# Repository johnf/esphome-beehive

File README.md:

# ESP32 Beehive Monitor

A battery-powered beehive monitoring system built with ESPHome. Uses FFT-based
audio analysis to detect colony health indicators, along with weight,
temperature, and humidity monitoring.

## Features

- **Audio Analysis**: FFT-based frequency band monitoring to detect queen
  piping, queenless conditions, and pre-swarm behaviour
- **Weight Monitoring**: Track hive weight changes using 4x 50kg load cells via
  NAU7802 ADC
- **Environmental Sensing**: Temperature and humidity via SHT40 sensor
- **Power Monitoring**: Solar current, voltage and power via INA226; battery voltage
  and state of charge via the FeatherS3D's onboard MAX17048 fuel gauge
- **Battery Optimised**: Deep sleep between 5-minute measurement cycles
- **Home Assistant Integration**: Automatic sensor discovery and state reporting

## Hardware Requirements

| Component | Description | Qty |
| ----------- | ------------- | ----- |
| [FeatherS3D](https://unexpectedmaker.com/feathers3d) (ESP32-S3) | Main microcontroller | 1 |
| INMP441 | I2S MEMS microphone (GPIO1, 3, 7) | 1 |
| [Adafruit NAU7802](https://www.adafruit.com/product/4538) | 24-bit ADC breakout | 1 |
| 50kg Load Cells | Half-bridge strain gauges | 4 |
| SHT40 | Temperature/humidity sensor | 1 |
| INA226 | Solar current/voltage/power monitor | 1 |
| CN3065 | Solar LiPo charge controller | 1 |
| [3.7V 2000mAh LiPo](https://core-electronics.com.au/polymer-lithium-ion-battery-2000mah-38459.html) | Battery (DW01+ PCM) | 1 |
| Solar panel | 6V nominal, 1W or larger (CN3065 input is rated for 6V panels) | 1 |
| Stripboard 24 x 41 holes | Main board (under the bottom board) | 1 |
| Stripboard 16 x 15 holes | Hive board (inside the brood box) | 1 |
| JST-XH 8-way socket and cable | Hive cable, one socket per board | 2 sockets, 1 cable |
| JST-XH 12-way socket and cable | Load cell socket (J_CELLS) | 1 |
| JST-XH 2-way socket | Solar in, charger in, charger out | 3 |
| JST-PH 2-way pigtail | CN3065 solar and output sockets | 2 |
| 100 nF ceramic capacitor | C2, C3 | 2 |
| 470 µF 6.3 V electrolytic capacitor | C1 | 1 |

## Power Architecture

The battery is charged by the CN3065 solar charge controller. An INA226 sits
high-side between the solar panel and the CN3065 solar input. The battery connects
directly to the CN3065 battery terminal.

The CN3065 output feeds the FeatherS3D's **VBAT pin**, so the board's own LDO
regulates 3.3V. Feeding the 3.3V pin instead would leave LDO2 unpowered, as its
input is the VBAT/USB node rather than the 3.3V rail.

The FeatherS3D's onboard charger only has power while USB is plugged in, so in the
field the CN3065 is the only charger. On USB, both chargers are 4.2V CC/CV parts and
share the cell harmlessly, with the DW01+ PCM as a backstop.

Battery voltage and state of charge come from the FeatherS3D's onboard MAX17048 fuel
gauge (I2C 0x36), which sees the cell via the VBAT pin. It sits on the always-on
LDO1 rail, so its ModelGauge state survives deep sleep.

The FeatherS3D's **LDO2** (GPIO39) provides a switchable 3.3V rail that is automatically
disabled during deep sleep, used to power-gate sensors that aren't needed during sleep.
All sensors, including the I2C pull-ups on their breakouts, are on this rail.

The INA226 address pins A0 and A1 are left unconnected. The CJMCU-226 module
has 10 kΩ pull-downs on both, which gives address 0x40. Confirm this on your
unit before building: unpowered, A0 to GND and A1 to GND should each read about
10 kΩ. If either reads open, strap that pad to GND.

CJMCU-226 modules come with two header pinouts: after ALE some read SDA then
SCL, others SCL then SDA. The Fritzing part (`fritzing/ina226/`) and the
stripboard layout follow the first, with SDA on pin 5. Check the silkscreen
before soldering the header; if yours is the other variant, do not plug the
module straight into its socket, but cross SDA and SCL with two short flying
leads.

### Solar Performance

The CN3065 regulates its own input voltage. In direct sun it held the panel at
4.77V for over an hour while the current drifted, well below the 6V maximum
power point of a nominal 6V panel. Panel power is therefore capped near 0.8W no
matter how much sun a 1W panel sees.

That cap matters less than it looks. The CN3065 is a linear charger, so it
passes current through roughly one-for-one and burns the voltage difference as
heat. Charge current, not panel watts, is what fills the cell.

Measured on a 110 x 60 mm 1W 6V polycrystalline panel in direct spring sun
(Sydney, sun about 52° above the horizon, panel not aimed):

| Quantity | Value |
|----------|-------|
| Panel voltage | 4.77V (clamped by the CN3065) |
| Panel current | 113-121 mA |
| Panel power | 0.54-0.58W |
| Fraction of nameplate | 55-58% |

At ~113 mA against an average draw of ~2.3 mA, roughly half an hour of direct
sun per day covers the device's entire daily consumption, and four good hours
put in over eight times what it uses. A 1W panel is ample for this load.

Siting buys far more than panel size. The same panel shaded and badly angled
produced 5-50 mW, one to two orders of magnitude below its direct-sun output,
and the battery fell 2.7% per day through it. If the battery is losing ground,
move the panel before buying a bigger one.

If you do want more margin, wire two panels in **parallel** to roughly double
the current at the clamped voltage. Series gains nothing, because the charger
regulates its input down regardless of what the panels could deliver.

### Battery Specifications

| Parameter | Value |
|-----------|-------|
| Nominal voltage | 3.7V |
| Charge voltage | 4.2V (CN3065) |
| Overcharge protection | 4.30V ±0.05V (DW01+ PCM) |
| Over-discharge protection | 2.4V ±0.1V (DW01+ PCM) |
| Capacity | 2000mAh |
| Wiring/connector rating | 1A max |

### I2C Address Map

| Address | Device |
|---------|--------|
| 0x2A | NAU7802 (load cell ADC) |
| 0x36 | MAX17048 fuel gauge (onboard FeatherS3D) |
| 0x40 | INA226 (solar) |
| 0x44 | SHT40 (temperature/humidity) |

## Wiring

The circuit is split across two stripboards joined by a pluggable cable. The
Fritzing sketch `fritzing/BeeHive.fzz` is the design of record and its
breadboard view holds the stripboard layout. Both boards use vertical strips
(strips run top to bottom in the breadboard view) and hole coordinates below
are `(column, row)` counted from 0 at the top-left.

### Boards and Connectors

**Main board** (24 x 41, under the bottom board with the battery, CN3065 and
solar panel plug): FeatherS3D, INA226, NAU7802, C1, C2 and five sockets. The
Feather sits across the top with its 16-pin row on row 3 and 12-pin row on
row 11; every strip under those rows is cut above the top row and below the
bottom row (cuts `x.3v` and `x.10v` for columns 3-18 and 3-14) so the two rows
do not short, except column 15, which carries the Feather GND pin the full
height of the board as the ground rail. Column 2 is the 3.3 V rail, fed from
LDO2 (column 3, row 3) by the jumper on row 2.

Columns 2-9 run straight from the Feather's bottom row to J_HIVE on the bottom
edge (row 40), so 3V3, SDA, SCL, WS, SCK and SD reach the hive socket without a
jumper; columns 5 and 6 (IO33 and IO38, cut at `5.11v 6.11v`) become its two
ground pins via row 14. Everything else sits to the right of that corridor:
C1 and the VBAT tap at the top right, J_PWR on the right edge at row 15, the
INA226 with its header on row 18 (VCC, GND, SCL, SDA, ALE, VBS, IN-, IN+ on
columns 14-21, GND landing on the rail, C2 directly above it on row 17),
J_SOLAR and J_CHG on the right edge at rows 28 and 31, the NAU7802 with its
header on row 29 (DRDY, SDA, SCL, GND, AVDD, VCC on columns 12-17, GND on the
rail, screw terminal facing the bottom edge) and J_CELLS on the bottom edge
beside J_HIVE. Column 23 is a second ground rail for C1 and the three
right-edge sockets; column 22 carries VBAT, panel + and charger + in three
segments. Row 39 stays empty under the two bottom sockets.

| Row | Jumper | Net |
| --- | ------ | --- |
| 2 | (3,2) → (2,2) | LDO2 to the 3.3 V rail |
| 12 | (14,12) → (22,12) | VBAT to C1 and J_PWR |
| 13 | (2,13) → (14,13) | 3.3 V to INA226 VCC and C2 |
| 13 | (15,13) → (23,13) | Ground to the right rail |
| 14 | (15,14) → (6,14) → (5,14) | Ground to J_HIVE pins 4 and 5 |
| 15 | (4,15) → (16,15) | SCL to the INA226 |
| 16 | (3,16) → (13,16) → (17,16) | SDA to the NAU7802 and INA226 |
| 26 | (14,26) → (17,26) | 3.3 V to NAU7802 VCC |
| 26 | (19,26) → (20,26) | INA226 VBS to IN- |
| 26 | (21,26) → (22,26) | INA226 IN+ to J_SOLAR + |
| 27 | (16,27) → (14,27) | SCL to the NAU7802 |
| 33 | (20,33) → (22,33) | INA226 IN- to J_CHG + |
| 38 | (12,38) → (13,38), (15,38) → (16,38), (18,38) → (19,38), (21,38) → (22,38) | Load cell ring, see [Load Cells](#load-cells) |
| 38 | (11,38), (14,38), (17,38), (20,38) | Flying leads into the NAU7802 screw terminal |

**Hive board** (16 x 15, inside the brood box): SHT40, INMP441, C3 and the
cable socket. It is wired up the inside of the hive and unplugs at the main
board.

| Socket | Board, holes | Pin 1 | Pin 2 | Pin 3 | Pin 4 | Pin 5 | Pin 6 | Pin 7 | Pin 8 |
| --- | --- | --- | --- | --- | --- | --- | --- | --- | --- |
| J_HIVE | Main (2-9, 40) | 3V3 | SDA | SCL | GND | GND | WS | SCK | SD |
| J_SUB | Hive (2-9, 1) | 3V3 | SDA | SCL | GND | GND | WS | SCK | SD |
| J_SOLAR | Main (22-23, 28) | Panel + | Panel - | | | | | | |
| J_CHG | Main (22-23, 31) | CN3065 SOLAR + | CN3065 SOLAR - | | | | | | |
| J_PWR | Main (22-23, 15) | CN3065 OUT + | CN3065 OUT - | | | | | | |
| J_CELLS | Main (11-22, 40) | 12 pins, see [Load Cells](#load-cells) | | | | | | | |

The hive cable is wired pin for pin. Ground sits between SCL and the I2S
clocks so the cable can run a metre or two. With Cat5e or Cat6, pair the wires
by signal, not in T568A/B order, which puts SCL with WS and SCK with SD:

| Pair | Pin | Signal | Colour |
| --- | --- | --- | --- |
| Blue | 7 | SCK | Blue |
| | 4 | GND | White/blue |
| Green | 3 | SCL | Green |
| | 5 | GND | White/green |
| Orange | 2 | SDA | Orange |
| | 1 | 3V3 | White/orange |
| Brown | 6 | WS | Brown |
| | 8 | SD | White/brown |

Each clock shares its pair with a ground. WS and SD can share a pair because
both change on the falling edge of SCK and SD is read on the rising edge. Keep
the untwisted length at each connector under about 15 mm.

JST-XH is 2.5 mm pitch, which
fits the 2.54 mm stripboard grid with a little lean on the 8-way socket and
about half a millimetre over the 12-way. Every socket sits on a board edge, so
side-entry (S*B-XH-A) or top-entry (B*B-XH-A) housings both work.

The CN3065 module is not on the stripboard. Its three JST-PH sockets take the
panel current from J_CHG (after the INA226 shunt), the battery directly, and
send the output to J_PWR via short pigtails. The INA226 address pads A0 and A1
are left open; the module pulls them down (see Power Architecture).

Strip cuts on the main board beyond the Feather rows: `5.11v 6.11v` turn the
IO33 and IO38 strips into the J_HIVE grounds, `14.12v` separates VBAT from the
3.3 V segment that feeds the INA226, `13.15v 16.14v 17.15v` keep the SDA and
SCL taps off the Feather pins and pads above them, `17.25v 14.26v 16.27v
12.28v` split the INA226 columns from the NAU7802 header (VCC, SCL, AVDD and
DRDY), `22.15v 22.29v` divide column 22 into VBAT, panel + and charger +, and
`11.37v` to `22.37v` isolate the J_CELLS pins (rows 38-40) from everything
above them. On the hive board the cuts are `6.4v` (SHT40 VIN off the ground
strip) and `10.6v 11.6v` (the microphone's top and bottom pin rows). The
sketch has the jumper wires and exact placements; check the build against it
with `python3 .claude/skills/circuit/fzz_nets.py fritzing/BeeHive.fzz`.

### I2C Bus (SHT40, NAU7802, INA226, MAX17048)

The I2C bus must be defined in your device configuration and its `id` passed to the
package via the `i2c_bus_id` substitution (defaults to `i2c_bus`).

| Signal | Default GPIO |
| -------- | ------------ |
| SDA | GPIO8 |
| SCL | GPIO9 |

### INMP441 Microphone

Pin assignments are configurable via substitutions (`i2s_lrclk_pin`, `i2s_bclk_pin`, `i2s_din_pin`).

| INMP441 Pin | Default ESP32 GPIO |
| ------------- | ------------ |
| WS (LRCLK) | GPIO1 |
| SCK (BCLK) | GPIO3 |
| SD (DOUT) | GPIO7 |
| VDD | 3.3V |
| GND | GND |
| L/R | GND (left channel) |

### Load Cells

Each 50kg half-bridge cell has three wires: red (centre tap), white and black.
All twelve go to J_CELLS, the 12-way JST-XH socket on the bottom edge of the
main board. The bridge is made on the board, so nothing is spliced at the
platform. Place one cell at each corner and number them 1 to 4 clockwise.

| J_CELLS pin | Wire | J_CELLS pin | Wire |
| ----------- | ---- | ----------- | ---- |
| 1 | Cell 1 red | 7 | Cell 3 red |
| 2 | Cell 1 white | 8 | Cell 3 white |
| 3 | Cell 2 white | 9 | Cell 4 white |
| 4 | Cell 2 red | 10 | Cell 4 red |
| 5 | Cell 2 black | 11 | Cell 4 black |
| 6 | Cell 3 black | 12 | Cell 1 black |

The jumpers on row 38 bridge pins 2-3, 5-6, 8-9 and 11-12, joining like
colours round the platform (white 1-2, black 2-3, white 3-4, black 4-1) into a
full Wheatstone bridge. Like must join like: in each cell the white and black
halves change in opposite directions under load, so a white-to-black ring
cancels in every bridge arm and the output barely moves. The four red wires
land on row 38 under the NAU7802 screw terminal and run into it with short
leads:

| Cell (red wire) | Row 38 hole | NAU7802 |
| --------------- | ----------- | ------- |
| Cell 1 | (11,38) | E+ |
| Cell 2 | (14,38) | A- |
| Cell 3 | (17,38) | E- |
| Cell 4 | (20,38) | A+ |

E+ and E- are the bridge excitation (the breakout's AVDD and GND); A- and A+
are the channel A input. The B- and B+ terminals are the unused channel B.

If the weight reads negative when load is added, swap A+ and A-.

### Capacitors

| Ref | Value | Placement |
| --- | ----- | --------- |
| C1 | 470 µF electrolytic, 6.3 V | VBAT and GND strips at the top right, main board (22-23, 11) |
| C2 | 100 nF ceramic | INA226 VCC and GND strips directly above its header, main board (14-15, 17) |
| C3 | 100 nF ceramic | INMP441 VDD and GND strips, hive board (11-12, 10) |

C1 stops WiFi transmit bursts browning out the LDO when the cell is cold or low.
C2 and C3 must sit right at the module pins; long wires in a beehive pick up
noise, and the INMP441 feeds the FFT analysis. The NAU7802 and SHT40 breakouts
have onboard decoupling already.

## Enclosure

`case/beehive-case.scad` is a parametric OpenSCAD model of two enclosures, with
exported STLs in `case/stl/`. Every dimension is a named variable at the top of
the file.

The `layout` view shows where the boards, battery and charger sit:

After changing a dimension, re-export the STLs and images:

```bash
cd case
for p in box lid clamp foot hive_base hive_lid; do
  openscad -D "part=\"$p\"" -o stl/$p.stl beehive-case.scad
done
openscad -D 'part="layout"' --camera=0,0,0,50,0,25,600 --viewall --autocenter \
  --imgsize=1600,1100 --colorscheme=Tomorrow -o images/layout.png beehive-case.scad
openscad -D 'part="layout"' --camera=0,0,0,0,0,0,600 --projection=ortho --viewall \
  --autocenter --imgsize=1600,1100 --colorscheme=Tomorrow -o images/layout-top.png \
  beehive-case.scad
openscad -D 'part="assembly"' --camera=0,0,0,50,0,25,600 --viewall --autocenter \
  --imgsize=1600,1100 --colorscheme=Tomorrow -o images/assembly.png beehive-case.scad
openscad -D 'part="seal_section"' --camera=0.99,37.98,0,0,0,0,40 --projection=ortho \
  --imgsize=1600,1100 --colorscheme=Tomorrow -o images/seal-section.png \
  beehive-case.scad
for p in hive_base hive_lid; do
  openscad -D "part=\"$([ $p = hive_lid ] && echo hive_lid_fitted || echo $p)\"" \
    --camera=0,0,0,50,0,25,150 --viewall --autocenter --imgsize=1600,1100 \
    --colorscheme=Tomorrow -o images/${p/_/-}.png beehive-case.scad
done
```

Then slice every STL with PrusaSlicer to catch parts that don't fit the bed or
need supports. `a1mini.ini` approximates the A1 mini with the settings below and
gives print times and filament use:

```bash
for p in box lid clamp foot hive_base hive_lid; do
  prusa-slicer --export-gcode --load a1mini.ini --center 90,90 \
    -o /tmp/$p.gcode stl/$p.stl 2>&1 | grep -A3 -i warning
done
```

`hive_lid` reports "Floating bridge anchors": that is the one-layer bridge over
each counterbore that you drill out, and it prints fine.

Open `beehive-case.scad` in OpenSCAD with `part = "layout"` to rotate the layout
view yourself. Colours only show in preview (F5), not in a full render (F6).

**Main box** sits under the hive and holds the main board, battery and CN3065.
The board rides on two M3 posts down its left edge and two printed clamps on its
right edge, with the battery and charger underneath. There is 30 mm clearance on
the terminal edges. Cables enter through two PG9 glands and a PG7 on one long wall; an
M12 ePTFE vent on the end wall lets it breathe without leaving a gap for ants. A
2.4 mm O-ring sits in a groove in the rim. The lid closes flush on the rim,
which squeezes the ring 25%, and screws into heat-set inserts in eight lugs. A
skirt under the lid locates it inside the walls, and a lip around its edge
stiffens it and keeps rain off the rim.

The seal is a 155 mm OD x 2.4 mm nitrile O-ring (about 150 mm ID). It stretches
about 2% to fit the groove, whose centre line is 488 mm (`groove_len`). A larger
2.4 mm ring or cord also works: cut it to 488 mm and butt-join the ends with
cyanoacrylate. For a different cross-section, change `oring_d`, `groove_depth`
(0.75 x the cross-section, rounded to a multiple of the layer height) and
`groove_w` (1.3 x).

**Hive housing** sits loose on the mesh floor inside the brood box. The base is
solid so the SHT40 reads hive air, not air through the mesh. The board rests on
ledges and ribs on the lid's side walls hold it down. The top and sides are a
grid of 2 mm holes, too small for bees. The Cat6 leaves through a notch at one
end, tied to an anchor.

Print in PLA, starting from the A1 mini 0.20 mm Standard profile with 4 wall
loops, 35% infill and no brim (`box` and `lid` are 175 mm long on a 180 mm
bed). Iron the top surface of `lid`, which is its sealing face. Print `lid` and
`hive_lid` as exported (outside face down). Each screw hole in `hive_lid` has a one-layer
bridge at the bottom of its counterbore; push a 3 mm drill through it after
printing. Press the heat-set inserts into the lid lugs, board posts, clamp
towers and hive housing posts with a soldering iron before assembly, flush or
just below the surface; the lid must sit flat on the lugs.

| Part | Qty |
| ---- | --- |
| `box`, `lid`, `hive_base`, `hive_lid` | 1 each |
| `clamp` | 2 |
| `foot` (glue into the floor) | 4 |
| PG9 cable gland, 4-8 mm (load cells, Cat6) | 2 |
| PG7 cable gland, 3-6.5 mm (solar) | 1 |
| M12 ePTFE breather vent | 1 |
| M3 x 10 socket head cap screw, stainless | 14 |
| M3 x 5.7 mm heat-set insert, 4.0 mm hole (e.g. ruthex) | 14 |
| O-ring, 155 mm OD x 2.4 mm, nitrile | 1 |
| Adhesive-lined heatshrink (load cell bundle, solar pair) | 2 |
| Silica gel sachet | 1 |
| Removable double-sided mounting strip (battery to floor, e.g. 3M Command) | 1 |

Drill the main board's two M3 holes in the outer left column, 15 mm and 73 mm
from the bottom edge. If you drill elsewhere, update `left_holes_y`.

## Installation

### Prerequisites

- Home Assistant with the ESPHome add-on installed

### Setup

1. **Create a new device in ESPHome**

   - Open the ESPHome dashboard in Home Assistant
   - Click **+ New Device**
   - Choose **Continue** then **Skip this step** (we'll use our own config)
   - Enter a name (e.g., `beehive-monitor`) and click **Next**
   - Select **ESP32** as the device type
   - Click **Skip** to skip the installation for now

2. **Edit the configuration**

   Click **Edit** on the new device and use the following configuration:

   ```yaml
   # Include the beehive monitoring package. `refresh: always` re-fetches the
   # default branch on every run instead of using ESPHome's cached copy.
   packages:
     beehive:
       url: https://github.com/johnf/esphome-beehive
       files: [beehive-monitor.yaml]
       refresh: always

   # Device configuration (required)
   esphome:
     name: beehive-monitor
     friendly_name: Beehive Monitor

   esp32:
     framework:
       type: esp-idf
     variant: esp32s3
     flash_size: 16MB  # FeatherS3D has 16MB flash

   psram:
     mode: quad
     speed: 80MHz

   # I2C bus (required - must define with id matching i2c_bus_id substitution)
   i2c:
     id: i2c_bus
     sda: GPIO8
     scl: GPIO9
     scan: true
     frequency: 400kHz

   # WiFi configuration (required)
   wifi:
     ssid: !secret wifi_ssid
     password: !secret wifi_password
     fast_connect: true

   # Home Assistant API (required)
   api:
     reboot_timeout: 0s

   # Optional: enable logging during development
   logger:
     hardware_uart: USB_CDC
     level: DEBUG

   # Optional: override default pin assignments, I2C addresses, calibration
   # or audio thresholds (see beehive-monitor.yaml for the full list)
   # substitutions:
   #   i2c_bus_id: "i2c_bus"
   #   i2s_lrclk_pin: "GPIO1"
   #   i2s_bclk_pin: "GPIO3"
   #   i2s_din_pin: "GPIO7"
   #   ina226_solar_address: "0x40"
   #   audio_active_threshold: "-95dB"
   ```

   A complete working example is in [example.yaml](example.yaml).

3. **Configure secrets**

   ESPHome uses Home Assistant's secrets. Add to your `secrets.yaml`:

   ```yaml
   wifi_ssid: 'YourWiFiNetwork'
   wifi_password: 'YourWiFiPassword'
   ```

   Or use the ESPHome Secrets editor (three-dot menu → **Secrets**).

4. **Install to the device**

   - Click **Install** on the device
   - For first-time installation, choose **Plug into this computer** or
     **Manual download** to get the firmware binary
   - Flash via USB using the web installer at <https://web.esphome.io/>
   - Subsequent updates can use **Wirelessly** once connected; see
     [OTA Updates](#ota-updates) for how to keep the device awake

### OTA Updates

The device is only awake for a few seconds every five minutes, which is not long
enough to install firmware wirelessly. The package therefore reads a Home
Assistant boolean helper on every wake and stays awake while it is on.

1. In Home Assistant, go to **Settings → Devices & services → Helpers**, create a
   **Toggle** helper and name it `Beehive OTA mode`, so its entity ID is
   `input_boolean.beehive_ota_mode`. Use the `ota_mode_entity` substitution if
   you pick a different name or run several hives.

   Then go to **Settings → Devices & services → ESPHome**, open the device's
   integration entry, click **Configure** and enable **Allow the device to
   perform Home Assistant actions**. The device needs this to clear the helper
   if it's left on (see below).
2. Turn the helper on. Within five minutes the device wakes, sees it, and logs
   `OTA mode - staying awake`. It keeps taking readings every
   `ota_mode_interval` (default five minutes); the **Measure Now** button
   starts a cycle straight away.
3. Click **Install → Wirelessly** in the ESPHome dashboard. Once an upload
   starts the device will not sleep until it reboots into the new firmware.
4. After the reboot the device stays awake while the helper is on, so you can
   watch the logs. Turn the helper off and the device goes back to sleep
   straight away.

If the helper is left on, the device clears it after `ota_mode_max_awake`
(default 30 minutes) and goes back to sleep. Without the actions permission
from step 1 the device still sleeps after the timeout, but stays awake again on
the next wake until you turn the helper off.

To check which commit a device is running, look at **Firmware** on the device
page in Home Assistant, or for `Project johnf.esphome-beehive version <commit>`
in the boot log. A `-dirty` suffix means it was built from a checkout with
uncommitted changes.

The package defines the `ota` component. To add a password or other options,
extend it in your device configuration rather than declaring a second one:

```yaml
ota:
  - id: !extend ota_esphome
    password: !secret ota_password
```

### Power Optimisation (recommended for battery operation)

For battery-powered deployments, add these settings to reduce power consumption:

```yaml
wifi:
  ssid: !secret wifi_ssid
  password: !secret wifi_password
  fast_connect: true
  power_save_mode: light
  # Static IP eliminates DHCP negotiation, saving 1-3 seconds per wake
  manual_ip:
    static_ip: 192.168.1.100  # Choose an IP outside your DHCP range
    gateway: 192.168.1.1      # Your router's IP
    subnet: 255.255.255.0

api:
  reboot_timeout: 0s  # Prevent reboots when Home Assistant is unavailable

# Disable UART logging in production
logger:
  level: WARN
  baud_rate: 0
```

## Calibration

### Load Cell Calibration

The package ships with placeholder calibration values that will not match your
load cells. Calibrate before trusting any weight reading.

1. Turn on [OTA mode](#ota-updates) so the device stays awake, and view the
   device logs in the ESPHome dashboard (click **Logs**). Each measurement
   cycle logs seven raw NAU7802 values; use the middle of the range. Cycles
   repeat every `ota_mode_interval` (default 5 minutes); set it to `10s` while
   calibrating for quicker readings, or press the **Measure Now** button on
   the device page in Home Assistant to start a cycle immediately
2. With no weight on the platform, note the raw value
3. Place a known weight on the platform and note the raw value. Use at least
   20 kg so the calibration spans a realistic hive weight; a second known
   weight (e.g. 40 kg) improves accuracy further
4. Let the platform settle for a minute after each change before reading
5. Click **Edit** on the device and set the calibration substitutions:

   ```yaml
   substitutions:
     weight_cal_raw_1: "<raw_empty>"
     weight_cal_kg_1: "0"
     weight_cal_raw_2: "<raw_20kg>"
     weight_cal_kg_2: "20"
     weight_cal_raw_3: "<raw_40kg>"
     weight_cal_kg_3: "40"
     weight_cal_raw_4: "<raw_40kg>"
     weight_cal_kg_4: "40"
   ```

   A least-squares line is fitted through the four points, so repeating a
   point is fine if you only have two known weights.

6. Click **Install** → **Wirelessly** to update the device

### Audio Baseline

Frequency band levels are reported as mean power spectral density in dB
relative to full scale (dB re FS²/Hz). This is independent of `fft_size` and
`frames`, so thresholds survive changes to those settings. Sound Level is
plain dBFS, measured above 60 Hz so the microphone's DC offset is excluded. The INMP441 reaches full scale at roughly 120 dB SPL, so add 120
to convert either figure to an approximate sound pressure level.

Each reading averages four consecutive FFT frames (about one second of audio).
Increase `audio_frames` for steadier band levels at the cost of awake time.

The Modulation Index and Modulation Frequency sensors come from a separate,
longer capture (`audio_modulation_duration`, default 10 s). Abdollahi et al.
(2026) found that the rate at which the buzz amplitude fluctuates predicts
colony strength far better than the average spectrum: weak colonies modulate
below 10 Hz, strong colonies spread up to about 35 Hz, and the 10-25 Hz range
is the most discriminating. The component takes a 100 ms / 12.5 ms hop STFT of
the 150-250 Hz band, then a second FFT over that envelope. Modulation Index is
the percentage of envelope power (1-40 Hz) that lies in 10-25 Hz, so it is
independent of microphone gain and colony loudness. Modulation Frequency is
the strongest modulation rate. Both are new and uncalibrated: log them for a
season alongside inspections before trusting them, and compare night-time
readings (roughly 8-11 pm, when foragers are home) rather than daytime ones.
The band and rate can be overridden with `modulation_band:` and
`modulation_rate:` blocks on the `bee_audio` component. Omit both modulation
sensors to skip the capture entirely and shorten awake time.

The classification thresholds are exposed as substitutions and will need
tuning for your microphone placement, hive size and background noise:

| Substitution | Default | Meaning |
|--------------|---------|---------|
| `audio_colony_prominence_threshold` | 3dB | Worker band less than this above the low-frequency band → `no_colony` |
| `audio_active_threshold` | -95dB | Worker band above this → `active` |
| `audio_normal_threshold` | -105dB | Baseline band above this → `normal`, below → `quiet` |
| `audio_queenless_threshold` | 6dB | Both queenless bands this far above baseline → `queenless` |
| `audio_queen_piping_threshold` | 10dB | Tooting or quacking this far above baseline → piping |
| `audio_pre_swarm_centroid` | 400Hz | Centroid above this while active → `pre_swarm` |
| `audio_modulation_duration` | 10s | Audio captured for the modulation spectrum (4-60 s) |

To tune, record the band sensors in Home Assistant for a few days and set
`audio_normal_threshold` between the quietest night-time baseline level and the
daytime level, and `audio_active_threshold` around the worker band level on a
busy afternoon. The band edges themselves can be overridden with a `bands:`
block on the `bee_audio` component, for example:

```yaml
bee_audio:
  bands:
    worker:
      low: 170Hz
      high: 280Hz
```

### Audio Baseline

The audio thresholds are set based on research values. You may need to adjust them in `components/bee_audio/bee_audio.cpp` based on:

- Microphone placement within the hive
- Hive size and colony population
- Background noise levels

## Sensors

### Frequency Bands

| Sensor | Frequency Range | Purpose |
|--------|-----------------|---------|
| Low Frequency | 60-100 Hz | Low frequency content |
| Baseline Hum | 100-200 Hz | Normal colony activity |
| Worker Activity | 180-260 Hz | Worker bee flight |
| Queen Quacking | 200-350 Hz | Virgin queen in cell |
| Queen Tooting | 350-500 Hz | Emerged virgin queen |
| Queenless Mid | 478-677 Hz | Queenless indicator |
| Queenless High | 876-1080 Hz | Queenless indicator |

### Derived Metrics

| Sensor | Unit | Description |
|--------|------|-------------|
| Dominant Frequency | Hz | Peak frequency in 60-600 Hz range |
| Sound Level | dB | RMS sound level above 60 Hz |
| Spectral Centroid | Hz | Centre of mass of spectrum |
| Modulation Index | % | Share of 150-250 Hz envelope power modulating at 10-25 Hz |
| Modulation Frequency | Hz | Strongest modulation rate of the 150-250 Hz envelope (1-40 Hz) |

### Power Monitoring

| Sensor | Unit | Description |
|--------|------|-------------|
| Solar Bus Voltage | V | Solar panel voltage |
| Solar Current | A | Current from solar panel |
| Solar Power | W | Solar power input |
| Battery Voltage | V | Cell voltage from the MAX17048 |
| Battery Level | % | State of charge from the MAX17048 ModelGauge |
| Solar Producing | on/off | Solar current above `charging_current_threshold`. Panel output, not net battery current: the device draws more than the charger supplies during the wake window, so the battery only gains during deep sleep |

### Hive State Classification

The system classifies the hive into one of these states:

| State | Description |
|-------|-------------|
| `quiet` | Very low activity, possibly night-time or cold |
| `normal` | Typical colony activity |
| `active` | Elevated worker activity |
| `queen_activity` | Queen piping detected (tooting or quacking) |
| `queenless` | Elevated mid/high frequency bands indicating queenless colony |
| `pre_swarm` | Elevated spectral centroid with high activity |
| `no_colony` | No bee hum: the worker band isn't above the low-frequency background. Checked first |

## Power Consumption

Indicative figures only; measure the real draw of your build with a meter in series
with the battery.

| State | Current Draw | Duration |
|-------|--------------|----------|
| Deep Sleep | ~10 µA (ESP32 only, sensor rail off) | Rest of the 5 minute cycle |
| Active | ~150 mA | ~15 seconds (~1.5 s audio, ~10 s modulation, ~1 s weight, WiFi connect) |
| **Average** | **~2.3 mA** | - |

The average is measured, not estimated: the fuel gauge fell 2.7% per day over
three days with the panel shaded, which is about 54 mAh/day out of 2000 mAh.

**Note**: Any sensor not powered from LDO2 draws standby current during deep
sleep.

With a 2000 mAh battery and no solar input at all, that 2.7% per day works out
to roughly a month from full. Any reasonable sun keeps it topped up
indefinitely; see [Solar Performance](#solar-performance).

## Home Assistant

Once connected, sensors will automatically appear in Home Assistant.

[dashboard.yaml](dashboard.yaml) is a ready-made dashboard with overview, audio and
power views. Create a new dashboard from scratch, open **Edit dashboard → Raw
configuration editor**, and paste the file in. Entity IDs assume the device is
named `Beehive Monitor`; replace `beehive_monitor_` if yours differs.

### Battery days remaining

The power view's "Days until flat" tile needs two helpers (Settings → Devices &
services → Helpers → Create helper):

1. **Statistics**, named `Beehive Monitor Battery Drain Rate`, on
   `sensor.beehive_monitor_battery_level`. Characteristic: *change per second*;
   sampling size 3000; max age 7 days; keep last sample on; precision 8.
2. **Template → sensor**, named `Beehive Monitor Battery Days Remaining`. Unit
   `d`, device class *duration*, state class *measurement*, device *Beehive
   Monitor*. State:

   ```jinja
   {% set rate = states('sensor.beehive_monitor_battery_drain_rate') | float %}
   {{ (states('sensor.beehive_monitor_battery_level') | float / (-rate * 86400)) | round(1) if rate < 0 else none }}
   ```

   Availability (under advanced options):

   ```jinja
   {{ has_value('sensor.beehive_monitor_battery_drain_rate') and has_value('sensor.beehive_monitor_battery_level') }}
   ```

The estimate is a straight line through the last week, which averages out the
day/night solar cycle. It reads unknown while the battery is holding or gaining
charge, and lags a week behind changes in the weather.

Example automations:

```yaml
automation:
  - alias: 'Alert on Queenless Hive'
    trigger:
      - platform: state
        entity_id: text_sensor.beehive_monitor_hive_state
        to: 'queenless'
        for:
          hours: 1
    action:
      - service: notify.mobile_app
        data:
          title: 'Beehive Alert'
          message: 'Hive may be queenless - check colony!'

  # Piping is detected from a one-second sample every five minutes, so a
  # single detection may be noise. Require it to persist across two readings.
  - alias: 'Alert on Queen Piping'
    trigger:
      - platform: state
        entity_id: binary_sensor.beehive_monitor_queen_piping_detected
        to: 'on'
        for:
          minutes: 6
    action:
      - service: notify.mobile_app
        data:
          title: 'Beehive Alert'
          message: 'Queen piping detected - possible swarm preparation'
```

## Troubleshooting

### No audio data

- Check INMP441 wiring, especially L/R pin (must be grounded for left channel)
- Verify 3.3V power supply is stable
- Check I2S pin assignments in YAML

### Weight barely changes under load

- A raw value near zero that moves by only tens of counts when you lean on the
  platform means the bridge is cancelling itself. Check the outer wires are
  joined white to white and black to black (see [Load Cells](#load-cells));
  expect a thousand or more counts per kilogram when wired correctly
- Each cell must be free to flex: support the outer frame and load the centre
  boss, or the reverse. A cell sitting flat on a surface cannot bend

### Weight readings unstable

- Ensure load cells are properly mounted and not touching the frame
- Check for loose connections on the NAU7802
- Recalibrate with weights spanning the real hive weight range; extrapolating
  from a few kilograms magnifies noise
- Each reading is already the median of seven raw samples; if the log shows
  "No measurements ready!" on every sample, or "weight not published", check
  the NAU7802 power and I2C

### WiFi connection issues

- Enable `fast_connect: true` to skip scanning
- Position the ESP32 antenna away from metal components
- Consider adding an external antenna

### Deep sleep not working

- Check that `on_boot` script is executing (visible in logs)
- Check the OTA mode helper is off in Home Assistant
- Verify no other components are blocking sleep
- Ensure the `run_duration` is sufficient for sensor readings

### "ESPHome is not permitted to perform Home Assistant actions"

The device tried to clear the OTA mode helper after `ota_mode_max_awake`.
Enable **Allow the device to perform Home Assistant actions** on the device's
ESPHome integration entry (see [OTA Updates](#ota-updates)), then turn the
helper off.

### Battery slowly discharging

Compare Solar Power against the figures in
[Solar Performance](#solar-performance). Around 0.5W and 110 mA at midday is a
healthy 1W panel; tens of milliwatts means it is shaded or badly angled, which
is by far the most common cause.

- Check Solar Bus Voltage. Near the cell voltage means the panel is not driving
  the charger; around 4.8V means it is
- Reposition the panel before replacing it, and watch for shade that only falls
  across it for part of the day
- Solar Current is sampled only during the wake window, so what the panel does
  during deep sleep is invisible

## Development

Clone the repository and build the example configuration, which uses the
component from the local `components/` directory rather than the pinned
release:

```bash
cat > secrets.yaml <<'EOF'
wifi_ssid: my-ssid
wifi_password: my-password
EOF
esphome config example.yaml
esphome compile example.yaml
```

CI runs the same two commands on every push and pull request.

`setup-dev.sh` clones ESPHome, ESP-IDF and ESP-DSP into `cdeps/` so that
`clangd` can resolve headers when editing the C++ component.

### Releasing

There are no releases. Device configurations track the default branch and
re-fetch it on every run, so a push to `main` reaches devices on their next
build.

## Contributing

Contributions are welcome! Please open an issue or submit a pull request.

## References

- [Bee Audio Analysis Research](https://www.ncbi.nlm.nih.gov/pmc/articles/PMC7506584/) - Scientific basis for frequency bands
- [Abdollahi et al. 2026, Modulation Tensorgrams for Colony Strength](https://arxiv.org/abs/2607.20386) - Basis for the modulation spectrum sensors
- [ESPHome Documentation](https://esphome.io/)
- [ESP-DSP Library](https://github.com/espressif/esp-dsp)
- <https://how2electronics.com/how-to-use-ina226-dc-current-sensor-with-arduino/>

## Licence

ISC License - See [LICENSE](LICENSE) for details.

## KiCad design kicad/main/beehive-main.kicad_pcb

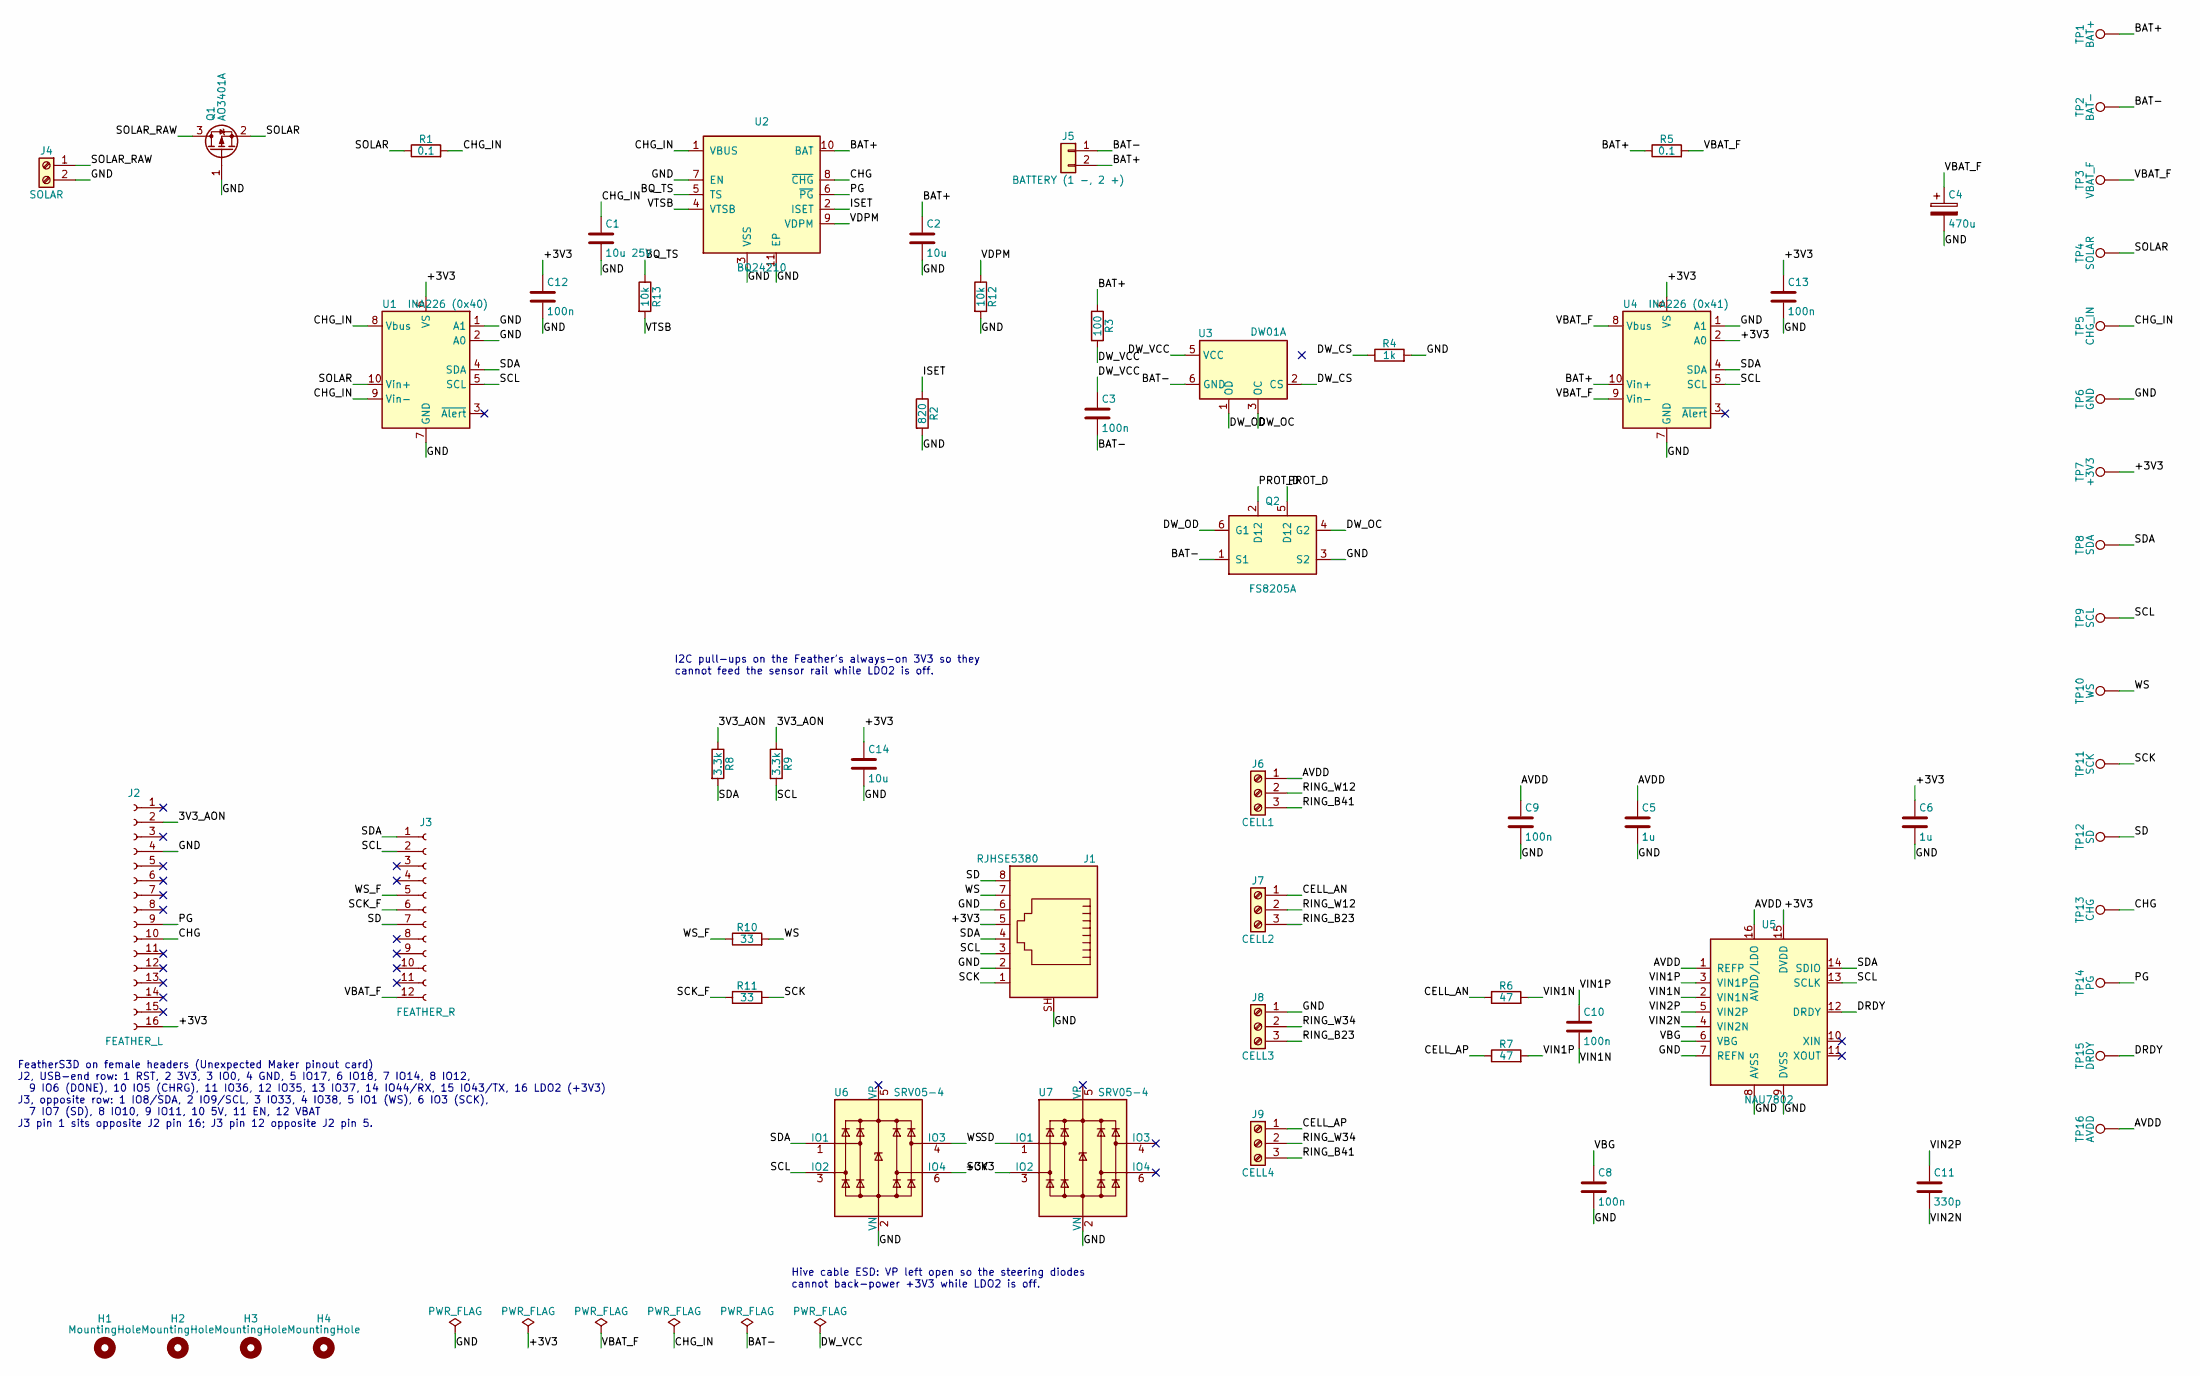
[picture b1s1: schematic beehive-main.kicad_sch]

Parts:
C1: 10u 25V; C_0603_1608Metric; LCSC C96446
C2, C14: 10u; C_0603_1608Metric; LCSC C19702
C3, C8, C9, C10, C12, C13: 100n; C_0603_1608Metric; LCSC C14663
C4: 470u; CP_Elec_6.3x7.7; MPN RVT1A471M0607; LCSC C335982
C5, C6: 1u; C_0603_1608Metric; LCSC C15849
C11: 330p; C_0603_1608Metric; LCSC C1664
H1, H2, H3, H4: MountingHole; MountingHole_3.2mm_M3
J1: RJHSE5380; RJ45_Amphenol_RJHSE5380; MPN RJHSE5380; LCSC C464586
J2: FEATHER_L; PinSocket_1x16_P2.54mm_Vertical; MPN KH-2.54FH-1X16P-H8.5; LCSC C2905421
J3: FEATHER_R; PinSocket_1x12_P2.54mm_Vertical; MPN KH-2.54FH-1X12P-H8.5; LCSC C2905419
J4: SOLAR; PhoenixContact_MC_1,5_2-G-3.5_1x02_P3.50mm_Horizontal; MPN DB2ERC-3.5-2P-GN; LCSC C395830
J5: BATTERY (1 -, 2 +); JST_PH_B2B-PH-K_1x02_P2.00mm_Vertical; MPN B2B-PH-K-S; LCSC C131337
J6: CELL1; PhoenixContact_MC_1,5_3-G-3.5_1x03_P3.50mm_Horizontal; MPN DB2ERC-3.5-3P-GN; LCSC C430551
J7: CELL2; PhoenixContact_MC_1,5_3-G-3.5_1x03_P3.50mm_Horizontal; MPN DB2ERC-3.5-3P-GN; LCSC C430551
J8: CELL3; PhoenixContact_MC_1,5_3-G-3.5_1x03_P3.50mm_Horizontal; MPN DB2ERC-3.5-3P-GN; LCSC C430551
J9: CELL4; PhoenixContact_MC_1,5_3-G-3.5_1x03_P3.50mm_Horizontal; MPN DB2ERC-3.5-3P-GN; LCSC C430551
Q1: AO3401A; SOT-23; LCSC C15127
Q2: FS8205A; SOT-23-6; LCSC C908265
R1, R5: 0.1; R_1206_3216Metric; LCSC C25334
R2: 820; R_0603_1608Metric; LCSC C23253
R3: 100; R_0603_1608Metric; LCSC C22775
R4: 1k; R_0603_1608Metric; LCSC C21190
R6, R7: 47; R_0603_1608Metric; LCSC C23182
R8, R9: 3.3k; R_0603_1608Metric; LCSC C22978
R10, R11: 33; R_0603_1608Metric; LCSC C23140
R12, R13: 10k; R_0603_1608Metric; LCSC C25804
TP1: BAT+; TestPoint_Pad_D1.5mm
TP2: BAT-; TestPoint_Pad_D1.5mm
TP3: VBAT_F; TestPoint_Pad_D1.5mm
TP4: SOLAR; TestPoint_Pad_D1.5mm
TP5: CHG_IN; TestPoint_Pad_D1.5mm
TP6: GND; TestPoint_Pad_D1.5mm
TP7: +3V3; TestPoint_Pad_D1.5mm
TP8: SDA; TestPoint_Pad_D1.5mm
TP9: SCL; TestPoint_Pad_D1.5mm
TP10: WS; TestPoint_Pad_D1.5mm
TP11: SCK; TestPoint_Pad_D1.5mm
TP12: SD; TestPoint_Pad_D1.5mm
TP13: CHG; TestPoint_Pad_D1.5mm
TP14: PG; TestPoint_Pad_D1.5mm
TP15: DRDY; TestPoint_Pad_D1.5mm
TP16: AVDD; TestPoint_Pad_D1.5mm
U1: INA226 (0x40); MSOP-10_3x3mm_P0.5mm; MPN INA226AIDGSR; LCSC C49851
U2: BQ24210; WSON-10-1EP_2x3mm_P0.5mm_EP0.84x2.4mm; MPN BQ24210DQCR; LCSC C524795
U3: DW01A; SOT-23-6; LCSC C351410
U4: INA226 (0x41); MSOP-10_3x3mm_P0.5mm; MPN INA226AIDGSR; LCSC C49851
U5: NAU7802; SOIC-16_3.9x9.9mm_P1.27mm; MPN NAU7802SGI; LCSC C2614351
U6, U7: SRV05-4; SOT-23-6; LCSC C558418

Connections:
/3V3_AON: J2.2, R8.1, R9.1
/+3V3: C6.1, C12.1, C13.1, C14.1, J1.5, J2.16, TP7.1 (1_1), U1.6 (VS), U4.2 (A0), U4.6 (VS), U5.15 (DVDD), U7.3 (IO2)
/AVDD: C5.1, C9.1, J6.1, TP16.1 (1_1), U5.1 (REFP), U5.16 (AVDD/LDO)
/BAT+: C2.1, J5.2, R3.1, R5.1, TP1.1 (1_1), U2.10 (BAT), U4.10 (Vin+)
/BAT-: C3.2, J5.1, Q2.1 (S1), TP2.1 (1_1), U3.6 (GND)
/BQ_TS: R13.1, U2.5 (TS)
/CELL_AN: J7.1, R6.1
/CELL_AP: J9.1, R7.1
/CHG: J2.10, TP13.1 (1_1), U2.8 (~CHG)
/CHG_IN: C1.1, R1.2, TP5.1 (1_1), U1.8 (Vbus), U1.9 (Vin-), U2.1 (VBUS)
/DRDY: TP15.1 (1_1), U5.12 (DRDY)
/DW_CS: R4.1, U3.2 (CS)
/DW_OC: Q2.4 (G2), U3.3 (OC)
/DW_OD: Q2.6 (G1), U3.1 (OD)
/DW_VCC: C3.1, R3.2, U3.5 (VCC)
/GND: C1.2, C2.2, C4.2, C5.2, C6.2, C8.2, C9.2, C12.2, C13.2, C14.2, J1.2, J1.6, J1.SH, J2.4, J4.2, J8.1, Q1.1 (G), Q2.3 (S2), R2.2, R4.2, R12.2, TP6.1 (1_1), U1.1 (A1), U1.2 (A0), U1.7 (GND), U2.3 (VSS), U2.7 (EN), U2.11 (EP), U4.1 (A1), U4.7 (GND), U5.7 (REFN), U5.8 (AVSS), U5.9 (DVSS), U6.2 (VN), U7.2 (VN)
/ISET: R2.1, U2.2 (ISET)
/PG: J2.9, TP14.1 (1_1), U2.6 (~PG)
/PROT_D: Q2.2 (D12), Q2.5 (D12)
/RING_B23: J7.3, J8.3
/RING_B41: J6.3, J9.3
/RING_W12: J6.2, J7.2
/RING_W34: J8.2, J9.2
/SCK: J1.1, R11.2, TP11.1 (1_1), U6.6 (IO4)
/SCK_F: J3.6, R11.1
/SCL: J1.3, J3.2, R9.2, TP9.1 (1_1), U1.5 (SCL), U4.5 (SCL), U5.13 (SCLK), U6.3 (IO2)
/SD: J1.8, J3.7, TP12.1 (1_1), U7.1 (IO1)
/SDA: J1.4, J3.1, R8.2, TP8.1 (1_1), U1.4 (SDA), U4.4 (SDA), U5.14 (SDIO), U6.1 (IO1)
/SOLAR: Q1.2 (S), R1.1, TP4.1 (1_1), U1.10 (Vin+)
/SOLAR_RAW: J4.1, Q1.3 (D)
/VBAT_F: C4.1, J3.12, R5.2, TP3.1 (1_1), U4.8 (Vbus), U4.9 (Vin-)
/VBG: C8.1, U5.6 (VBG)
/VDPM: R12.1, U2.9 (VDPM)
/VIN1N: C10.2, R6.2, U5.2 (VIN1N)
/VIN1P: C10.1, R7.2, U5.3 (VIN1P)
/VIN2N: C11.2, U5.4 (VIN2N)
/VIN2P: C11.1, U5.5 (VIN2P)
/VTSB: R13.2, U2.4 (VTSB)
/WS: J1.7, R10.2, TP10.1 (1_1), U6.4 (IO3)
/WS_F: J3.5, R10.1

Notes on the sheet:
Hive cable ESD: VP left open so the steering diodes cannot back-power +3V3 while LDO2 is off.
FeatherS3D on female headers (Unexpected Maker pinout card) J2, USB-end row: 1 RST, 2 3V3, 3 IO0, 4 GND, 5 IO17, 6 IO18, 7 IO14, 8 IO12, 9 IO6 (DONE), 10 IO5 (CHRG), 11 IO36, 12 IO35, 13 IO37, 14 IO44/RX, 15 IO43/TX, 16 LDO2 (+3V3) J3, opposite row: 1 IO8/SDA, 2 IO9/SCL, 3 IO33, 4 IO38, 5 IO1 (WS),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
I2C pull-ups on the Feather's always-on 3V3 so they cannot feed the sensor rail while LDO2 is off.

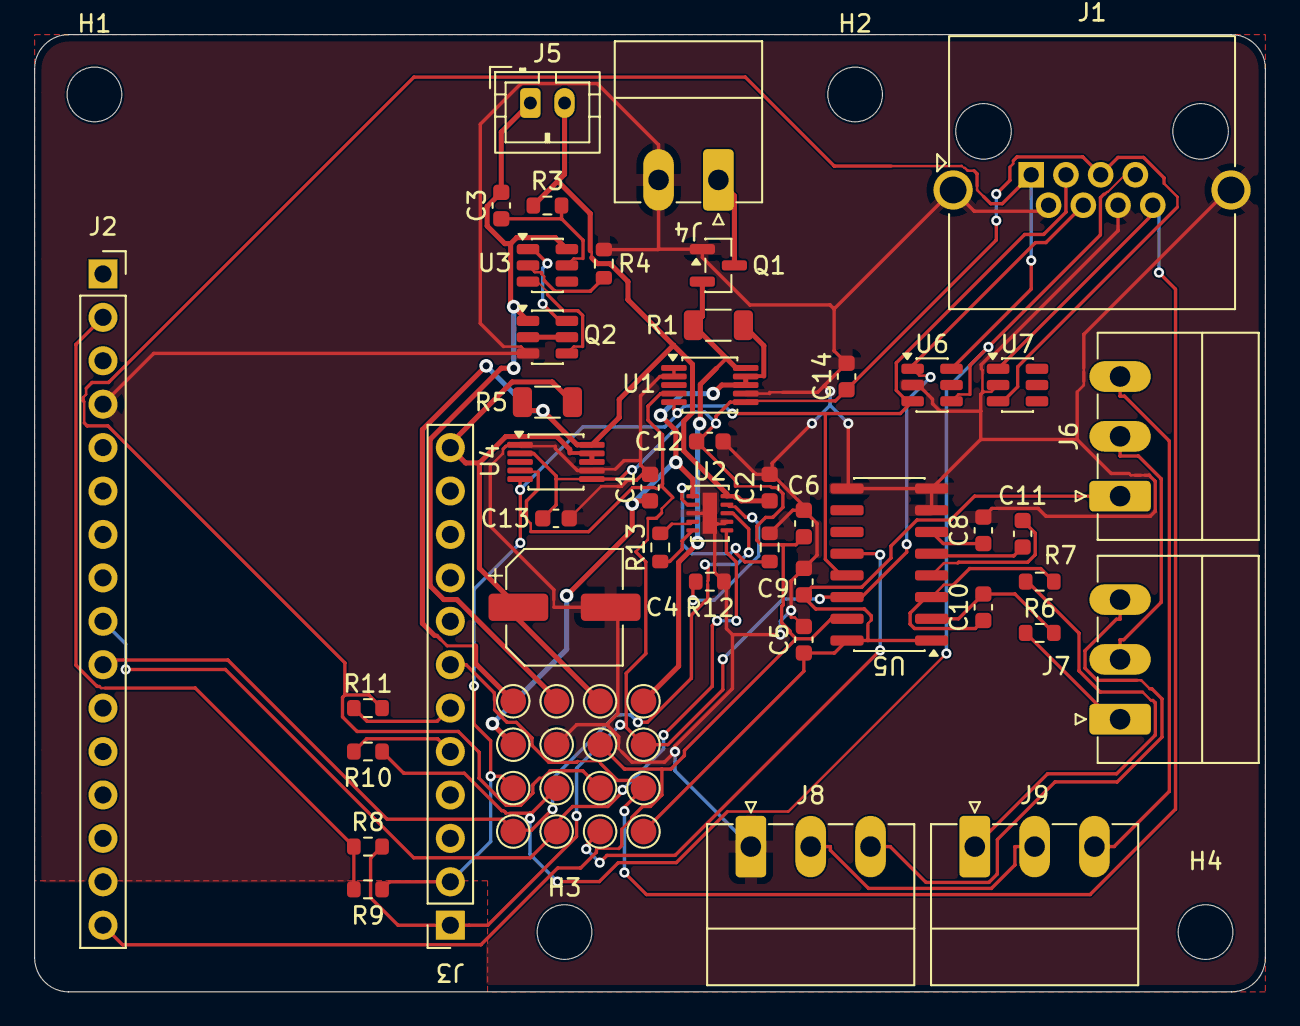
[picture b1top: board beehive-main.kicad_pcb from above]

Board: 2 copper layers, 72.0 x 56.0 mm, 64 parts (0 on the bottom side), 40 nets.

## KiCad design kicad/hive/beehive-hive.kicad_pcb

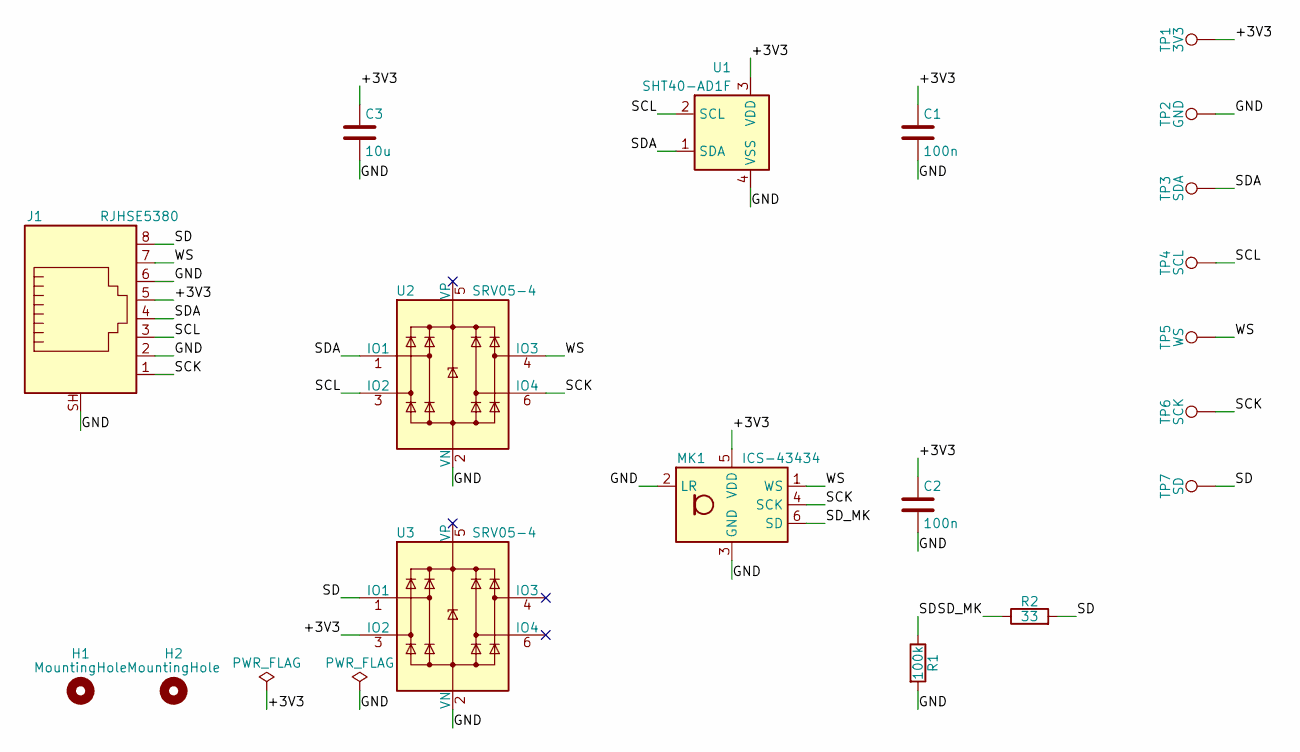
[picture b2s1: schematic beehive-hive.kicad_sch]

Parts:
C1, C2: 100n; C_0603_1608Metric; LCSC C14663
C3: 10u; C_0603_1608Metric; LCSC C19702
H1, H2: MountingHole; MountingHole_3.2mm_M3
J1: RJHSE5380; RJ45_Amphenol_RJHSE5380; MPN RJHSE5380; LCSC C464586
MK1: ICS-43434; InvenSense_ICS-43434-6_3.5x2.65mm; MPN ICS-43434; LCSC C5656610
R1: 100k; R_0603_1608Metric; LCSC C25803
R2: 33; R_0603_1608Metric; LCSC C23140
TP1: 3V3; TestPoint_Pad_D1.5mm
TP2: GND; TestPoint_Pad_D1.5mm
TP3: SDA; TestPoint_Pad_D1.5mm
TP4: SCL; TestPoint_Pad_D1.5mm
TP5: WS; TestPoint_Pad_D1.5mm
TP6: SCK; TestPoint_Pad_D1.5mm
TP7: SD; TestPoint_Pad_D1.5mm
U1: SHT40-AD1F; Sensirion_DFN-4_1.5x1.5mm_P0.8mm_SHT4x_NoCentralPad; MPN SHT40-AD1F-R2; LCSC C7461846
U2, U3: SRV05-4; SOT-23-6; LCSC C558418

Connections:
/+3V3: C1.1, C2.1, C3.1, J1.5, MK1.5 (VDD), TP1.1 (1_1), U1.3 (VDD), U3.3 (IO2)
/GND: C1.2, C2.2, C3.2, J1.2, J1.6, J1.SH, MK1.2 (LR), MK1.3 (GND), R1.2, TP2.1 (1_1), U1.4 (VSS), U2.2 (VN), U3.2 (VN)
/SCK: J1.1, MK1.4 (SCK), TP6.1 (1_1), U2.6 (IO4)
/SCL: J1.3, TP4.1 (1_1), U1.2 (SCL), U2.3 (IO2)
/SD: J1.8, R1.1, R2.2, TP7.1 (1_1), U3.1 (IO1)
/SDA: J1.4, TP3.1 (1_1), U1.1 (SDA), U2.1 (IO1)
/SD_MK: MK1.6 (SD), R2.1
/WS: J1.7, MK1.1 (WS), TP5.1 (1_1), U2.4 (IO3)

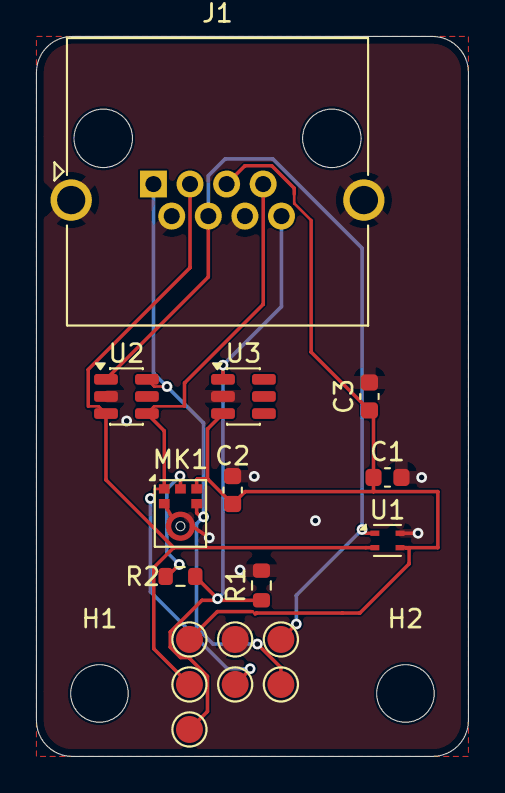
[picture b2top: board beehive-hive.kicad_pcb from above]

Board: 2 copper layers, 24.0 x 40.0 mm, 19 parts (0 on the bottom side), 8 nets.

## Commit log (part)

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2026-01-25 WIP: initial commit
2026-01-25 WIP: debug
2026-01-25 refactor(bee_audio): improve resource management and performance
    - Add destructor for proper I2S and buffer cleanup
    - Validate FFT size is power of 2 during setup
    - Cache band powers once per update cycle instead of recalculating
    - Add buffer sizes to allocation error messages for debugging
    - Use inline constexpr for frequency band constants (C++17)
    - Fix typo: "grabage" → "garbage"
2026-01-25 docs: fix I2S BCLK pin assignment and add configurable parameters
    Update CLAUDE.md and README.md to reflect the correct I2S BCLK pin
    (GPIO32 instead of GPIO26). Add documentation for configurable
    sample_rate and fft_size parameters in CLAUDE.md.
    Also includes minor formatting fixes in bee_audio.cpp.
2026-01-25 refactor: convert beehive-monitor.yaml to reusable ESPHome package
    Move device-specific configuration to user responsibility:
    - Remove esphome name/friendly_name, esp32, wifi, api, logger sections
    - Users now include this as a package and provide their own config
    Enable power optimisations by default:
    - Enable deep_sleep component (was commented out)
    - Set sensor update_interval to never (manual trigger only)
2026-01-25 fix: add SHT4x sensor to measurement cycle
    The temperature/humidity sensor was not being explicitly updated in the
    collect_and_sleep script. Add id and update_interval: never to match
    other sensors, and include in the measurement script.
2026-01-26 fix(bee_audio): remove invalid override from destructor
    PollingComponent doesn't declare a virtual destructor, so the override
    keyword causes a compilation error.
2026-01-31 refactor: expose I2C bus and I2S pins as configurable substitutions
    Remove hardcoded i2c bus definition from the package so users define
    their own bus externally and pass the id via i2c_bus_id substitution.
    Expose I2S GPIO pins (LRCLK, BCLK, DIN) as substitutions with updated
    defaults (GPIO1, 3, 7). Update README and CLAUDE.md with usage examples.
2026-01-31 feat: add prevent deep sleep switch for OTA updates and debugging
    Add a Home Assistant-controllable template switch that prevents deep
    sleep, allowing OTA updates and debugging. When enabled, the device
    stays awake and continues collecting sensor data every 5 minutes.
2026-01-31 feat: disable deep sleep when GPIO pin is high at boot
    Add a configurable GPIO pin (default GPIO11) with pulldown that
    prevents deep sleep when held high during boot, enabling OTA updates
    and debugging without Home Assistant access.
2026-04-13 feat: add fritzing schematic
2026-04-13 feat: add INA226 power monitoring, LDO2 sensor power gating, and battery level estimation
    - Add dual INA226 current/voltage/power sensors (solar 0x40, battery 0x45)
    with configurable I2C addresses via substitutions
    - Add sensor power switch (GPIO39/LDO2) owned by the package, with
    on_boot at priority 750 to power sensors before I2C setup runs
    - Add battery level sensor derived from INA226 bus voltage using a
    LiPo discharge curve (DW01+ PCM: 4.30V overcharge, 2.4V cutoff)
